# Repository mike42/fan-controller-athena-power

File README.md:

# PC Fan Controller for Athena Power Cases

This repository contains the circuit board and firmware for a fan controller which I designed to replace the splitter which ships with the Athena Power RM-1UC138 rackmount computer case.

Instead of running the bundled 12 V fans at full speed, this controller allows you to install your own PWM fans, and set a fixed speed via a potentiometer, with no involvement from the motherboard.

## Parts list

| Qty. | Description                      | Installed at   | Product ref.                                                                                                 |
|------|----------------------------------|----------------|--------------------------------------------------------------------------------------------------------------|
|    1 | 0.1 µF ceramic capacitor         | C1             | [Adafruit 753](https://www.adafruit.com/product/753)                                                         |
|    1 | PC power "Molex" connector       | J1             | [Sparkfun PRT-15700](https://www.sparkfun.com/products/15700)                                                |
|    4 | 4-pin PC fan header              | M1, M2, M3, M4 | [Molex 47053-1000](https://au.mouser.com/ProductDetail/Molex/47053-1000)                                     |
|    1 | 10 kΩ Potentiometer 0.1" spacing | RV1            | [Core Electronics CE09096](https://core-electronics.com.au/breadboard-compatible-potentiometer-10k-ohm.html) |
|    1 | ATtiny85 microcontroller         | U1             | [ATtiny85-20P](https://au.mouser.com/ProductDetail/Microchip-Technology/ATTINY85-20PU)                       |
|    1 | Optional: DIP-8 socket           | U1             | [TE 1-2199298-2](https://au.mouser.com/ProductDetail/TE-Connectivity/1-2199298-2)                            |

## More info

- [Controlling computer fans with a microcontroller](https://mike42.me/blog/2023-09-controlling-computer-fans-with-a-microcontroller) - which shows the use of a TL-866II+ to program the ATtiny85.
- [Building a 1U quiet NAS](https://mike42.me/blog/2023-10-building-a-1u-quiet-nas) - information about the computer build which this project was created for.

## Licensing 

While you are free to use these files to build this project yourself, you do so at your own risk. No warranty or support is offered.

The code for the ATTINY85 microcontroller is based on "[4-Wire-FAN-Arduino](https://github.com/marceloaqno/4-Wire-FAN-Arduino/blob/master/ATtiny_PWM_Phase_Corret_25kHz.ino)" by Marcelo Aquino, which is licensed under the GNU GPL.

The hardware files in this repository are additionally licensed under the [Creative Commons Attribution 4.0 International License](https://creativecommons.org/licenses/by/4.0/).

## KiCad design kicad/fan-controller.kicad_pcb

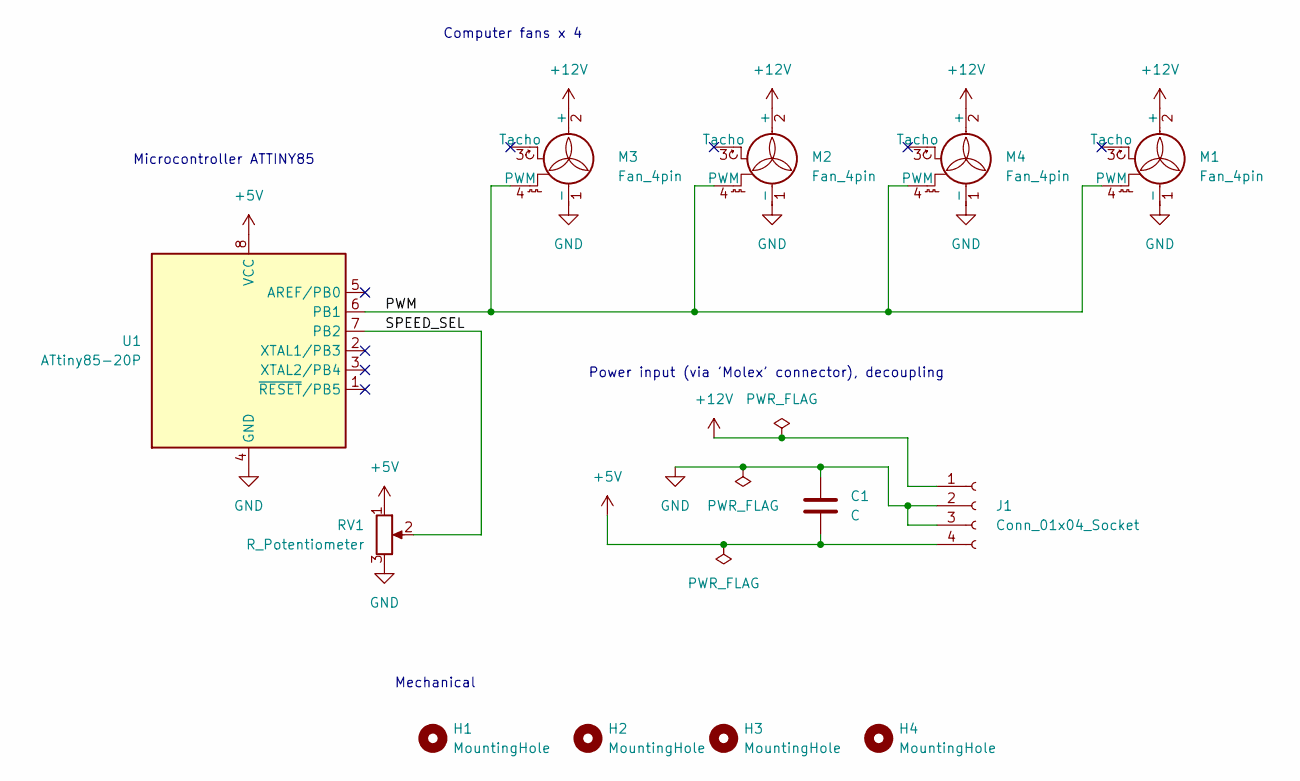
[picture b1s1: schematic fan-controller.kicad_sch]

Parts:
C1: C; C_Disc_D3.0mm_W2.0mm_P2.50mm
H1, H2, H3, H4: MountingHole; MountingHole_3.5mm
J1: Conn_01x04_Socket; PC_Molex_Power
M1, M2, M3, M4: Fan_4pin; FanPinHeader_1x04_P2.54mm_Vertical
RV1: R_Potentiometer; PinHeader_1x03_P2.54mm_Vertical
U1: ATtiny85-20P; DIP-8_W7.62mm

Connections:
+5V: C1.2, J1.4, RV1.1, U1.8 (VCC)
+12V: J1.1, M1.2 (+), M2.2 (+), M3.2 (+), M4.2 (+)
/PWM: M1.4 (PWM), M2.4 (PWM), M3.4 (PWM), M4.4 (PWM), U1.6 (PB1)
/SPEED_SEL: RV1.2, U1.7 (PB2)
GND: C1.1, J1.2, J1.3, M1.1 (-), M2.1 (-), M3.1 (-), M4.1 (-), RV1.3, U1.4 (GND)

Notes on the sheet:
Mechanical
Microcontroller ATTINY85
Computer fans x 4
Power input (via 'Molex' connector), decoupling

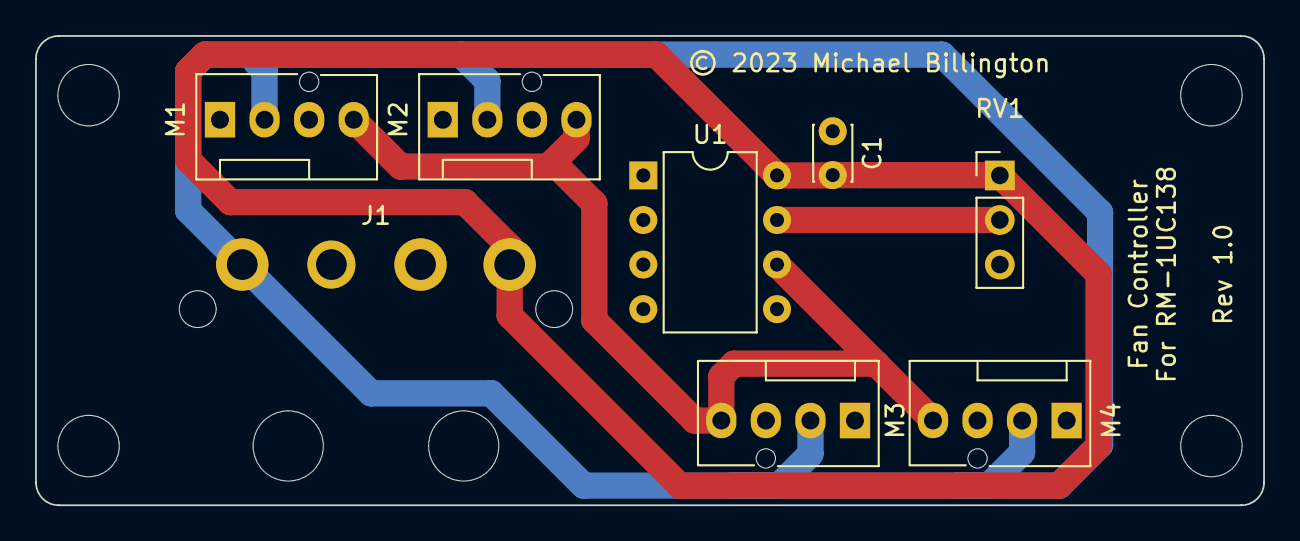
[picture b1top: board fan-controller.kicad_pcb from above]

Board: 2 copper layers, 70.0 x 26.8 mm, 12 parts (0 on the bottom side), 5 nets.

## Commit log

2023-10-20 initial commit - no parts list
2023-10-20 Update README.md
    add parts list, more info link
2023-12-04 Add link to completed build blog post

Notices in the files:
kicad/fan-controller.kicad_pcb:
© 2023 Michael Billington
